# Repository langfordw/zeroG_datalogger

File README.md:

# zeroG_datalogger
Datalogging code for Zero-G flight

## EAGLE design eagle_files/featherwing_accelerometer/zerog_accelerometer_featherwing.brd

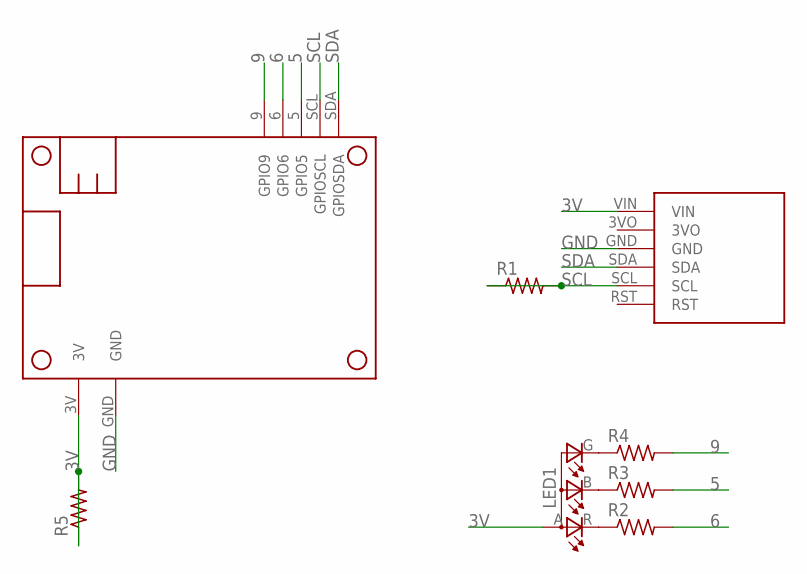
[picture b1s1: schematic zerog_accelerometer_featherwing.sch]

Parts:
LED1: LEDRGBOLD; P-LCC-4-3
R1, R2, R3, R4, R5: RES-US1206FAB; R1206FAB
U$1: FEATHERWING_I2C
U$2: BNO055_BREAKOUT

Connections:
3V: LED1.A (A2), R5.1, R5.2, U$1.3V, U$2.VIN
5: R3.2, U$1.5 (GPIO5)
6: R2.2, U$1.6 (GPIO6)
9: R4.2, U$1.9 (GPIO9)
GND: U$1.GND, U$2.GND
unnamed: LED1.R (CRED), R2.1
unnamed: LED1.B (CBLUE), R3.1
unnamed: LED1.G (CGREEN), R4.1
SCL: R1.1, R1.2, U$1.SCL (GPIOSCL), U$2.SCL
SDA: U$1.SDA (GPIOSDA), U$2.SDA

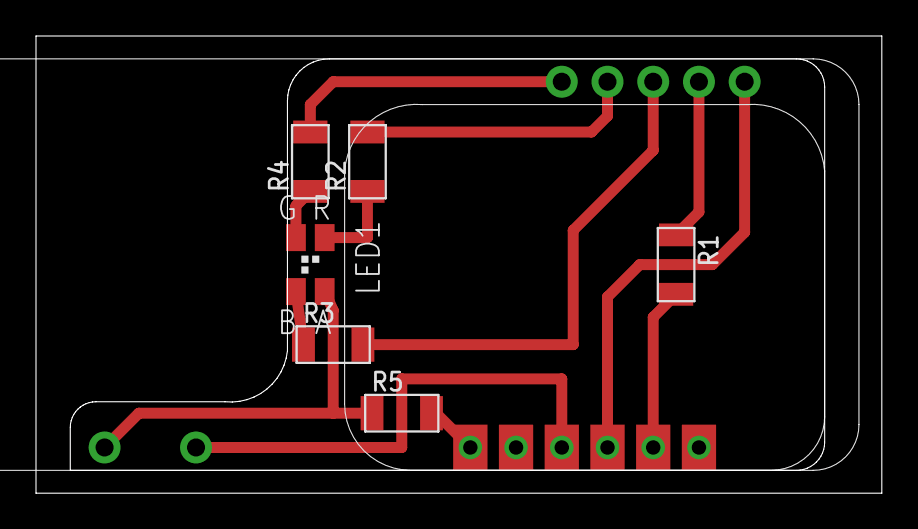
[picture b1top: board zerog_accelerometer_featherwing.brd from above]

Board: 2 copper layers, 47.0 x 25.4 mm, 8 parts (0 on the bottom side), 10 nets.

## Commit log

2017-03-19 adding eagle files and export
2017-03-19 adding structure logger code
2017-03-20 working on structure, sd not working great
2017-03-20 sd works by itself
2017-03-20 rx and sd working
2017-03-21 starting plotting
2017-03-21 adding day 1 data
2017-03-22 adding day1 sd
2017-03-23 adding day2 data
